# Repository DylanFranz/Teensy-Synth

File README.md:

# Teensy-Synth
A portable digital audio workstation and synthesizer

A project by Dylan Franz and Val Revankar

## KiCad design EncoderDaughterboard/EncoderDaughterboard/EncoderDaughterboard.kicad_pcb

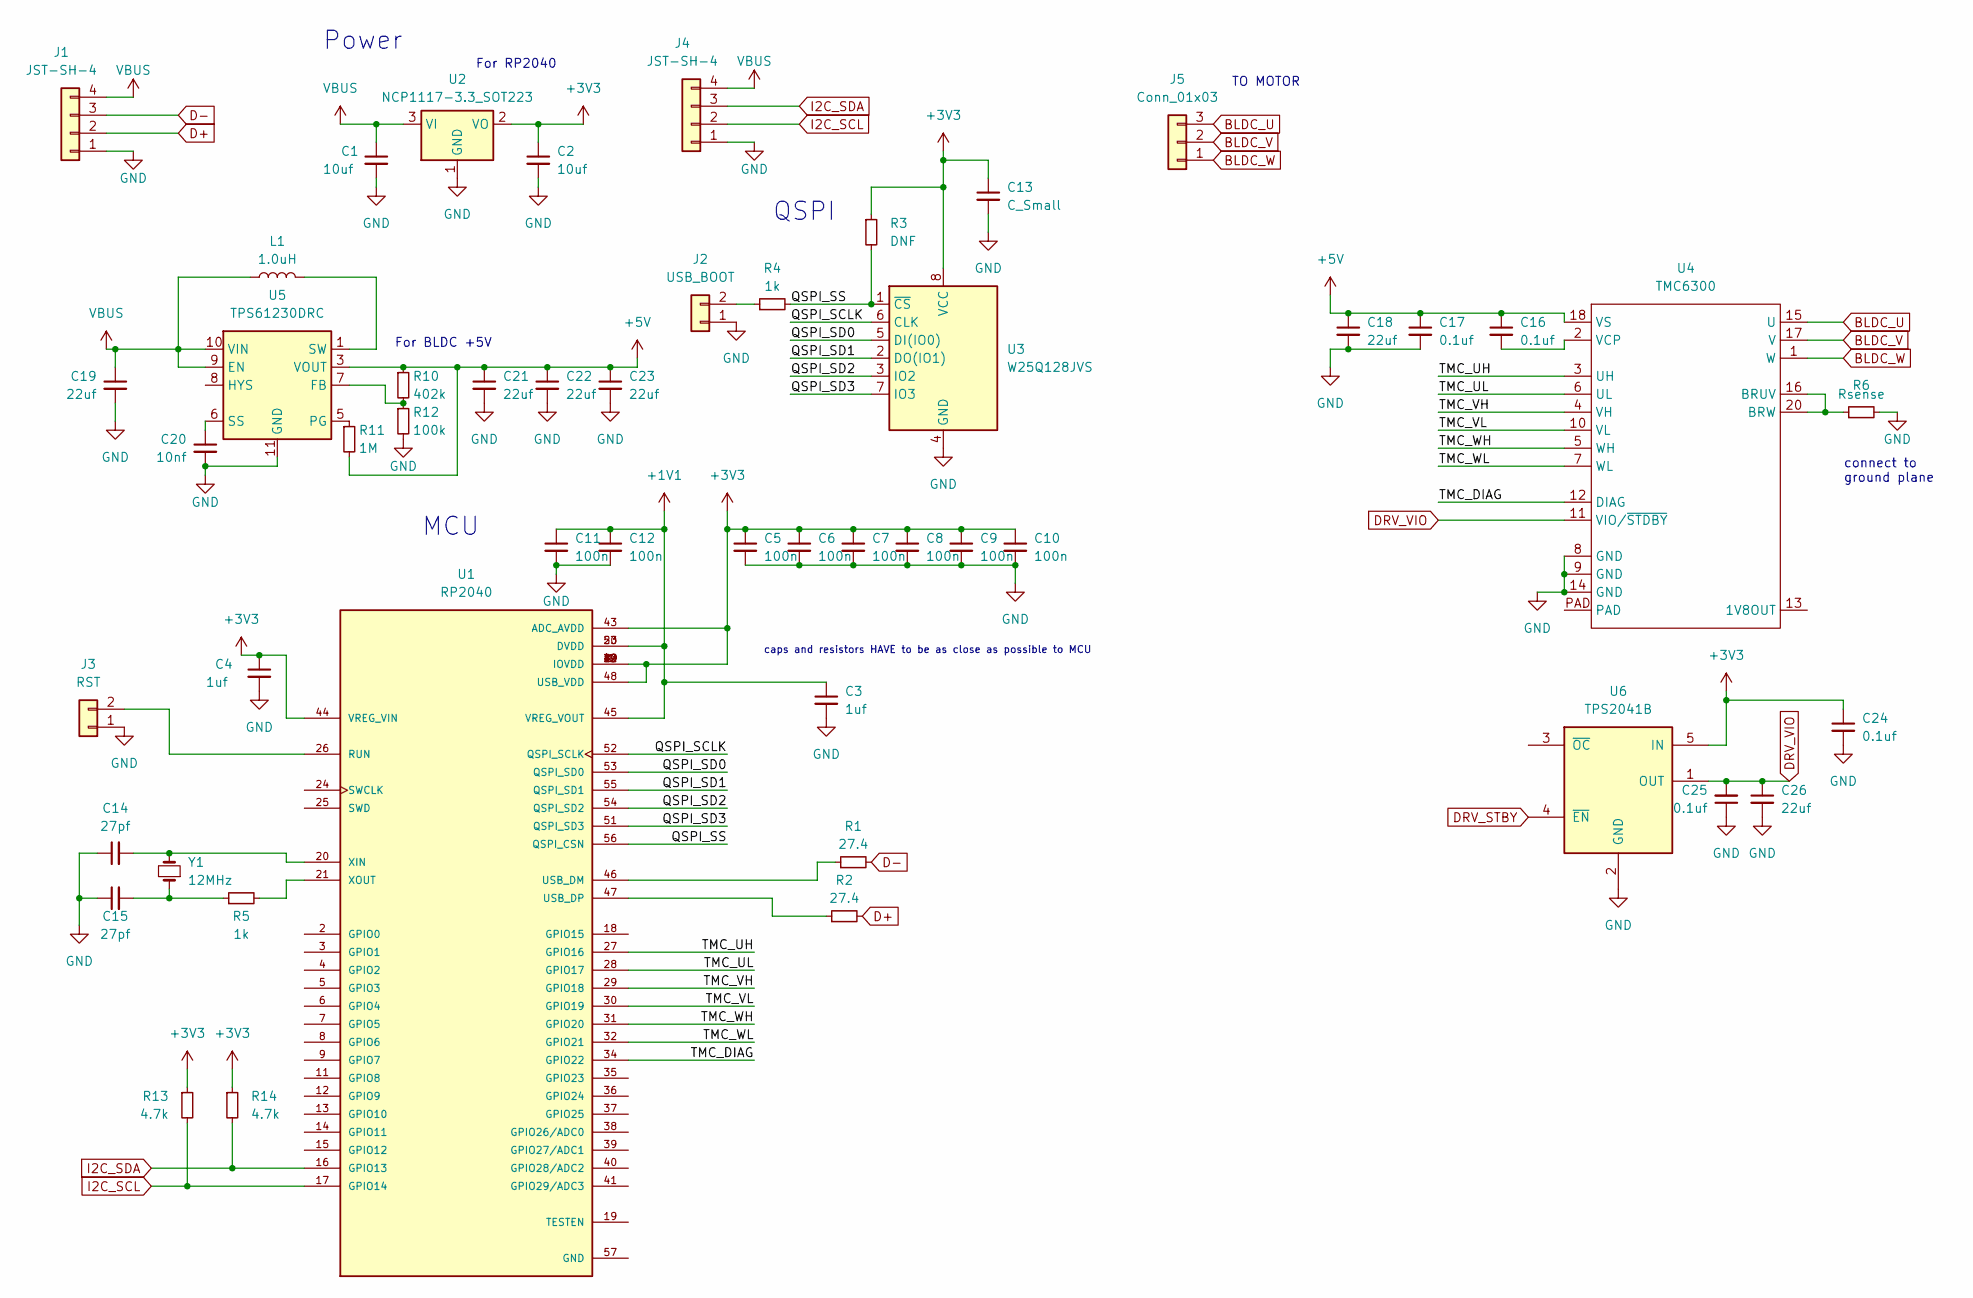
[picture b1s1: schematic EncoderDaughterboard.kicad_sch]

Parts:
C1, C2: 10uf; C_0402_1005Metric
C3, C4: 1uf; C_0402_1005Metric
C5, C6, C7, C8, C9, C10, C11, C12: 100n; C_0402_1005Metric
C13: C_Small; C_0402_1005Metric
C14, C15: 27pf; C_0402_1005Metric
C16, C17, C24, C25: 0.1uf; C_0402_1005Metric
C18, C19, C21, C22, C23, C26: 22uf; C_0402_1005Metric
C20: 10nf; C_0402_1005Metric
J1, J4: JST-SH-4; JST_SH_BM04B-SRSS-TB_1x04-1MP_P1.00mm_Vertical
J2: USB_BOOT; PinHeader_1x02_P1.00mm_Horizontal
J3: RST; PinHeader_1x02_P1.00mm_Horizontal
J5: Conn_01x03; PinHeader_1x03_P1.27mm_Vertical
L1: 1.0uH; L_0805_2012Metric
R1, R2: 27.4; R_0402_1005Metric
R3: DNF; R_0402_1005Metric
R4, R5: 1k; R_0402_1005Metric
R6: Rsense; R_0402_1005Metric
R10: 402k; R_0402_1005Metric
R11: 1M; R_0402_1005Metric
R12: 100k; R_0402_1005Metric
R13, R14: 4.7k; R_0402_1005Metric
U1: RP2040; QFN40P700X700X90-57N; PARTREV 1.6.1
U2: NCP1117-3.3_SOT223; SOT-223-3_TabPin2
U3: W25Q128JVS; SOIC-8_5.23x5.23mm_P1.27mm
U4: TMC6300; QFN20_3x3_TRI
U5: TPS61230DRC; Texas_S-PVSON-N10_ThermalVias
U6: TPS2041B; SOT-23-5
Y1: 12MHz; Crystal_SMD_0603-2Pin_6.0x3.5mm

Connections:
+1V1: C3.1, C11.1, C12.1, U1.23 (DVDD), U1.45 (VREG_VOUT), U1.50 (DVDD)
+3V3: C2.1, C4.1, C5.1, C6.1, C7.1, C8.1, C9.1, C10.1, C13.1, C24.1, R3.1, R13.1, R14.1, U1.1 (IOVDD), U1.10 (IOVDD), U1.22 (IOVDD), U1.33 (IOVDD), U1.42 (IOVDD), U1.43 (ADC_AVDD), U1.44 (VREG_VIN), U1.48 (USB_VDD), U1.49 (IOVDD), U2.2 (VO), U3.8 (VCC), U6.5 (IN)
+5V: C16.1, C17.1, C18.1, C21.1, C22.1, C23.1, R10.1, R11.2, U4.18 (VS), U5.3 (VOUT), U5.4 (VOUT)
/QSPI_SCLK: U1.52 (QSPI_SCLK), U3.6 (CLK)
/QSPI_SD0: U1.53 (QSPI_SD0), U3.5 (DI(IO0))
/QSPI_SD1: U1.55 (QSPI_SD1), U3.2 (DO(IO1))
/QSPI_SD2: U1.54 (QSPI_SD2), U3.3 (IO2)
/QSPI_SD3: U1.51 (QSPI_SD3), U3.7 (IO3)
/QSPI_SS: R3.2, R4.2, U1.56 (QSPI_CSN), U3.1 (~CS)
/TMC_DIAG: U1.34 (GPIO22), U4.12 (DIAG)
/TMC_UH: U1.27 (GPIO16), U4.3 (UH)
/TMC_UL: U1.28 (GPIO17), U4.6 (UL)
/TMC_VH: U1.29 (GPIO18), U4.4 (VH)
/TMC_VL: U1.30 (GPIO19), U4.10 (VL)
/TMC_WH: U1.31 (GPIO20), U4.5 (WH)
/TMC_WL: U1.32 (GPIO21), U4.7 (WL)
BLDC_U: J5.3, U4.15 (U)
BLDC_V: J5.2, U4.17 (V)
BLDC_W: J5.1, U4.1 (W)
D+: J1.2, R2.2
D-: J1.3, R1.2
DRV_STBY: U6.4 (~EN)
DRV_VIO: C25.2, C26.1, U4.11 (VIO/~STDBY), U6.1 (OUT)
GND: C1.2, C2.2, C3.2, C4.2, C5.2, C6.2, C7.2, C8.2, C9.2, C10.2, C11.2, C12.2, C13.2, C14.1, C15.1, C17.2, C18.2, C19.2, C20.2, C21.2, C22.2, C23.2, C24.2, C25.1, C26.2, J1.1, J2.1, J3.1, J4.1, R6.2, R12.2, U2.1 (GND), U3.4 (GND), U4.8 (GND), U4.9 (GND), U4.14 (GND), U5.11 (GND), U6.2 (GND)
I2C_SCL: J4.2, R13.2, U1.17 (GPIO14)
I2C_SDA: J4.3, R14.2, U1.16 (GPIO13)
unnamed: C15.2, R5.1, Y1.1
unnamed: J2.2, R4.1
unnamed: J3.2, U1.26 (RUN)
unnamed: L1.2, U5.1 (SW), U5.2 (SW)
unnamed: R1.1, U1.46 (USB_DM)
unnamed: R2.1, U1.47 (USB_DP)
unnamed: C14.2, U1.20 (XIN), Y1.2
unnamed: R5.2, U1.21 (XOUT)
unnamed: R6.1, U4.16 (BRUV), U4.20 (BRW)
unnamed: C16.2, U4.2 (VCP)
unnamed: R10.2, R12.1, U5.7 (FB)
unnamed: R11.1, U5.5 (PG)
unnamed: C20.1, U5.6 (SS)
VBUS: C1.1, C19.1, J1.4, J4.4, L1.1, U2.3 (VI), U5.9 (EN), U5.10 (VIN)

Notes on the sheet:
For BLDC +5V
connect to ground plane
Power
caps and resistors HAVE to be as close as possible to MCU
MCU
QSPI
TO MOTOR
For RP2040

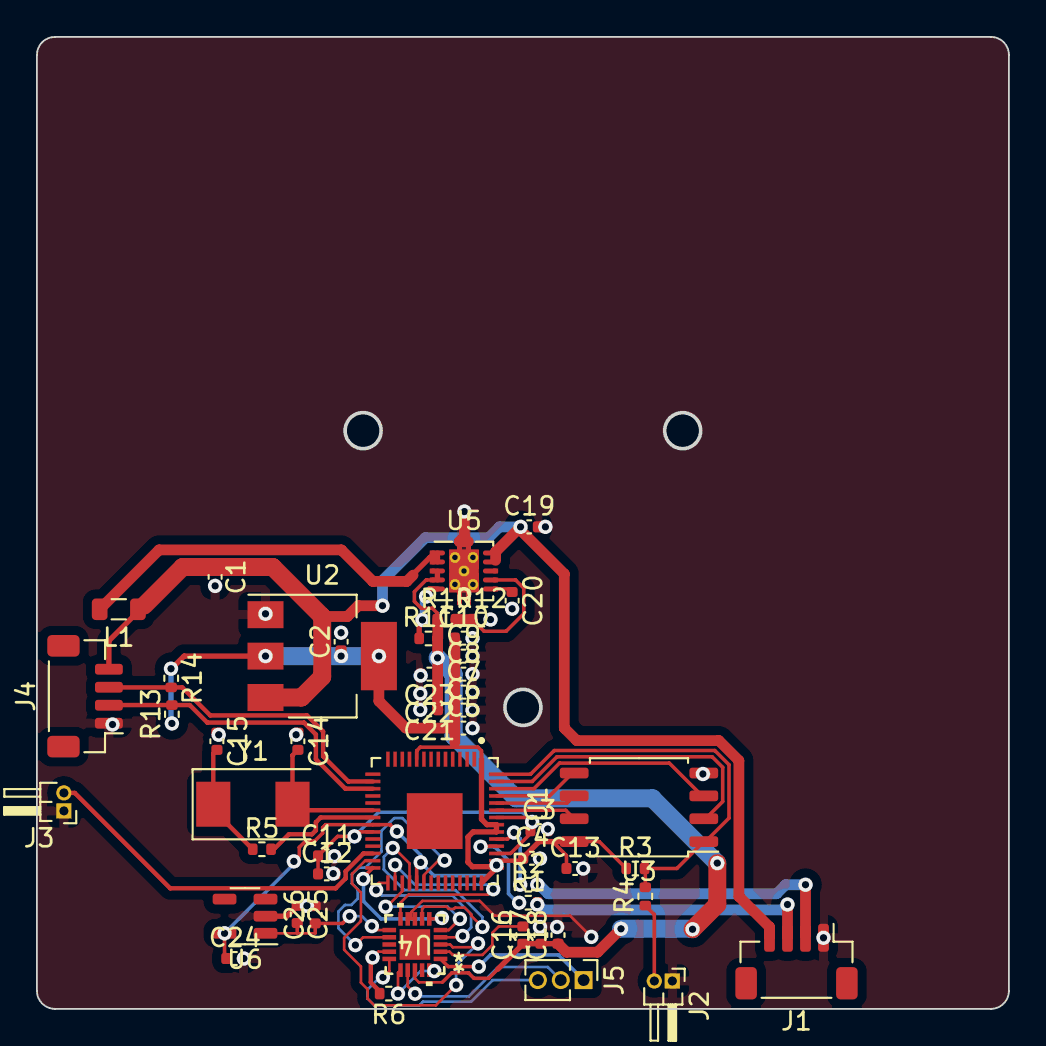
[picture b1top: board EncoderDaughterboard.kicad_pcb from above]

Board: 2 copper layers, 53.9 x 53.9 mm, 50 parts (0 on the bottom side), 39 nets.

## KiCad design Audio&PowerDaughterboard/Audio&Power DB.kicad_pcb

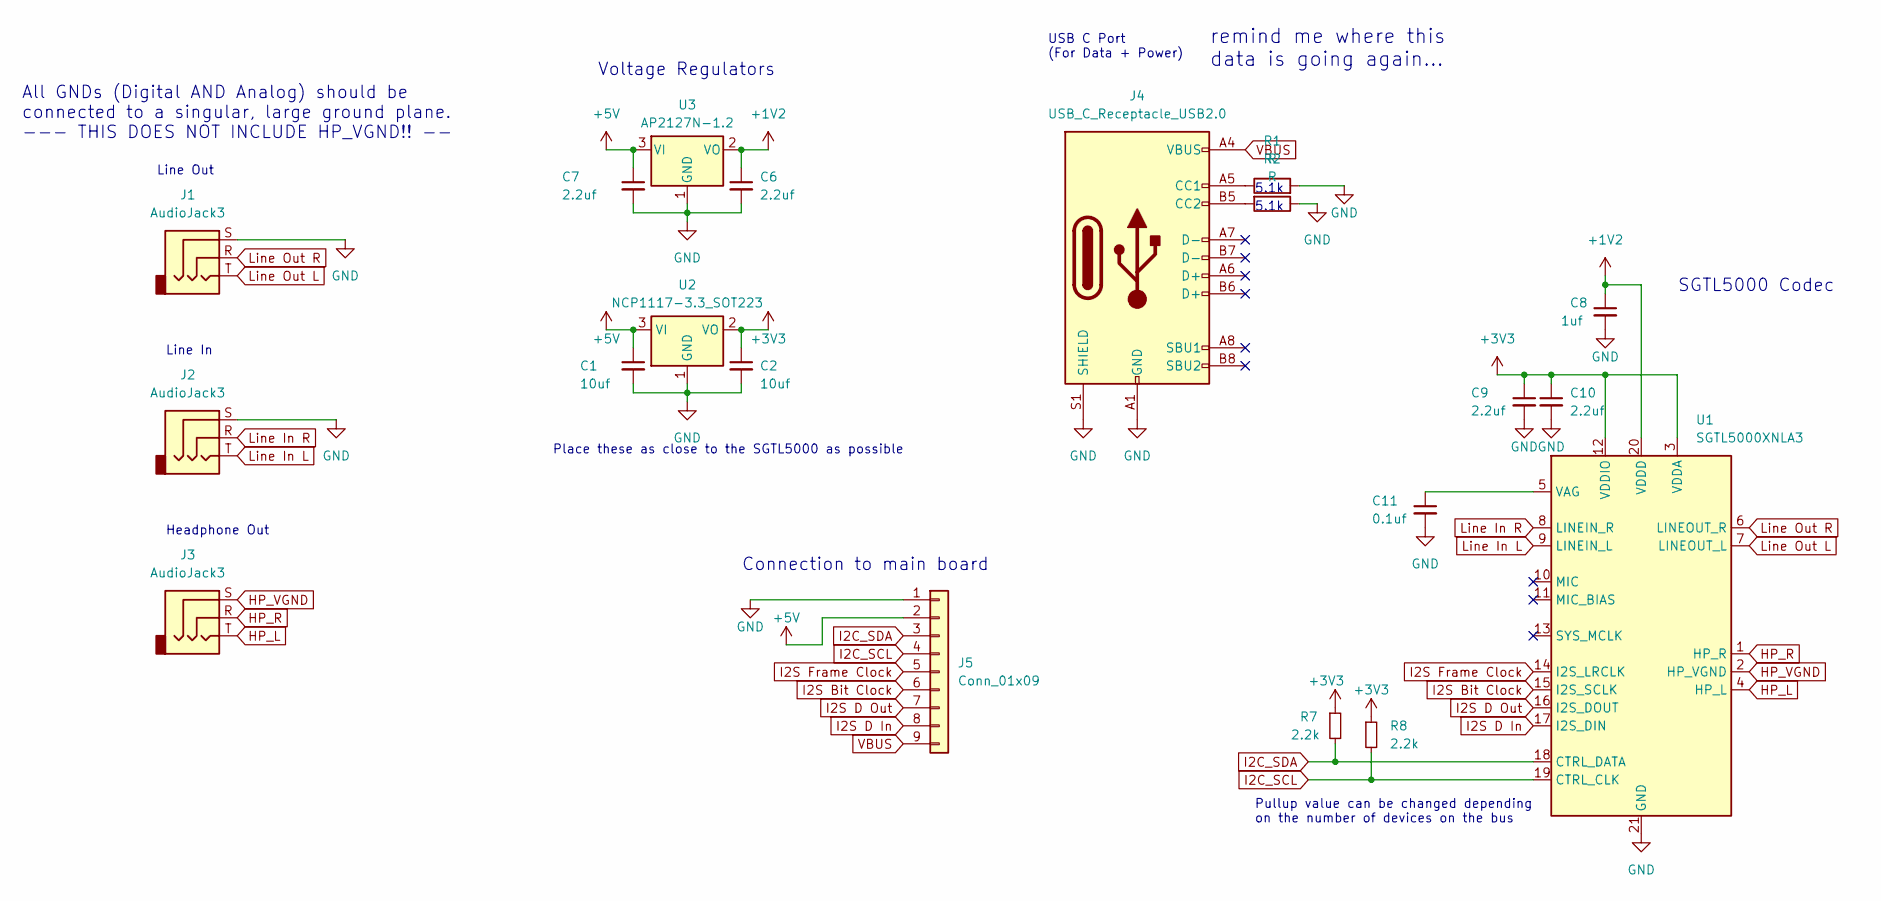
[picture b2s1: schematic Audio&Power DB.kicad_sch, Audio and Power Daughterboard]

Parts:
C1, C2: 10uf; C_0603_1608Metric
C6, C7, C9, C10: 2.2uf; C_0603_1608Metric
C8: 1uf; C_0603_1608Metric
C11: 0.1uf; C_0603_1608Metric
J1, J2, J3: AudioJack3; Jack_3.5mm_CUI_SJ-3523-SMT_Horizontal
J4: USB_C_Receptacle_USB2.0; USB_C_Receptacle_HRO_TYPE-C-31-M-12
J5: Conn_01x09; JST_SH_SM09B-SRSS-TB_1x09-1MP_P1.00mm_Horizontal
R1, R2: R; R_0603_1608Metric
R7, R8: 2.2k; R_0603_1608Metric
U1: SGTL5000XNLA3; QFN-20-1EP_3x3mm_P0.4mm_EP1.65x1.65mm
U2: NCP1117-3.3_SOT223; SOT-223-3_TabPin2
U3: AP2127N-1.2; SOT-23

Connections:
+1V2: C6.1, C8.1, U1.20 (VDDD), U3.2 (VO)
+3V3: C2.1, C9.1, C10.1, R7.1, R8.1, U1.3 (VDDA), U1.12 (VDDIO), U2.2 (VO)
+5V: C1.1, C7.1, J5.2, U2.3 (VI), U3.3 (VI)
GND: C1.2, C2.2, C6.2, C7.2, C8.2, C9.2, C10.2, C11.2, J1.S, J2.S, J4.A1 (GND), J4.A12 (GND), J4.B1 (GND), J4.B12 (GND), J4.S1 (SHIELD), J5.1, R1.2, R2.1, U1.21 (GND), U2.1 (GND), U3.1 (GND)
HP_L: J3.T, U1.4 (HP_L)
HP_R: J3.R, U1.1 (HP_R)
HP_VGND: J3.S, U1.2 (HP_VGND)
I2C_SCL: J5.4, R8.2, U1.19 (CTRL_CLK)
I2C_SDA: J5.3, R7.2, U1.18 (CTRL_DATA)
I2S Bit Clock: J5.6, U1.15 (I2S_SCLK)
I2S D In: J5.8, U1.17 (I2S_DIN)
I2S D Out: J5.7, U1.16 (I2S_DOUT)
I2S Frame Clock: J5.5, U1.14 (I2S_LRCLK)
Line In L: J2.T, U1.9 (LINEIN_L)
Line In R: J2.R, U1.8 (LINEIN_R)
Line Out L: J1.T, U1.7 (LINEOUT_L)
Line Out R: J1.R, U1.6 (LINEOUT_R)
unnamed: J4.A5 (CC1), R1.1
unnamed: J4.B5 (CC2), R2.2
unnamed: C11.1, U1.5 (VAG)
VBUS: J4.A4 (VBUS), J4.A9 (VBUS), J4.B4 (VBUS), J4.B9 (VBUS), J5.9

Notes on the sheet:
Voltage Regulators
Pullup value can be changed depending on the number of devices on the bus
5.1k
remind me where this data is going again...
Line In
USB C Port (For Data + Power)
Headphone Out
Place these as close to the SGTL5000 as possible
All GNDs (Digital AND Analog) should be connected to a singular, large ground plane. --- THIS DOES NOT INCLUDE HP_VGND!! --
SGTL5000 Codec
Line Out
Connection to main board

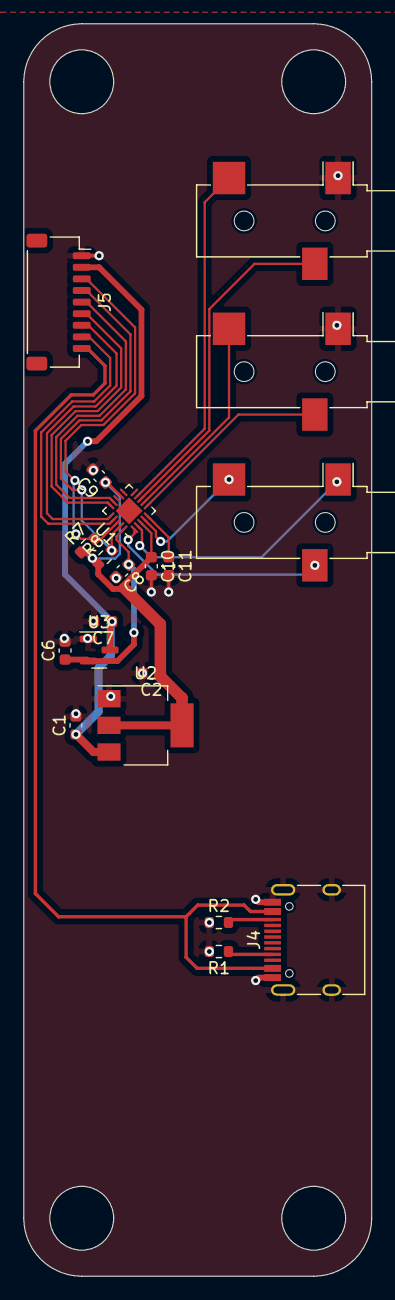
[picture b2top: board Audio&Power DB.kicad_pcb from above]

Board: 2 copper layers, 30.0 x 108.0 mm, 20 parts (0 on the bottom side), 21 nets.

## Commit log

2023-09-12 Added Matrix and MCUs
2023-09-12 Updated Matrix and MCUs
2023-09-12 Added MCUs and Matrix Labels
2023-09-12 Addded encoders (4+1)
2023-09-12 Fixed and Labeled Encoders
2023-09-12 Added Screen Pins
2023-09-13 Added EncoderDaughterboard and Firmware folders
2023-09-22 THE COMMIT TO END ALL COMMITS
2023-09-25 VAL FIX POWER PLS
2023-09-27 Power Daughterboard fully revised
2023-09-27 Fuck this shi
2023-09-29 Connected the button grid to the RP2040
2023-10-02 more hookups
2023-10-02 VAL PLS CONNECT AND COMMIT
2023-10-02 im using github desktop
    wahhhh my cli
2023-10-03 Mounting Holes LOL
2023-10-03 LOL 3d Models for APDB
2023-10-05 encoder daughterboard
2023-10-12 Finished Enc. DB Schematic
    enter routing hell
2023-10-16 footprint
    footprint
2023-10-17 Val pls dxf
2023-10-23 The Spaghetti has been cooked
    I am so sorry
2023-10-23 added motor conection VIAs
2023-10-25 over 100 DRC errors but hey weve got a render!
    :sleepdepriveddylan:
